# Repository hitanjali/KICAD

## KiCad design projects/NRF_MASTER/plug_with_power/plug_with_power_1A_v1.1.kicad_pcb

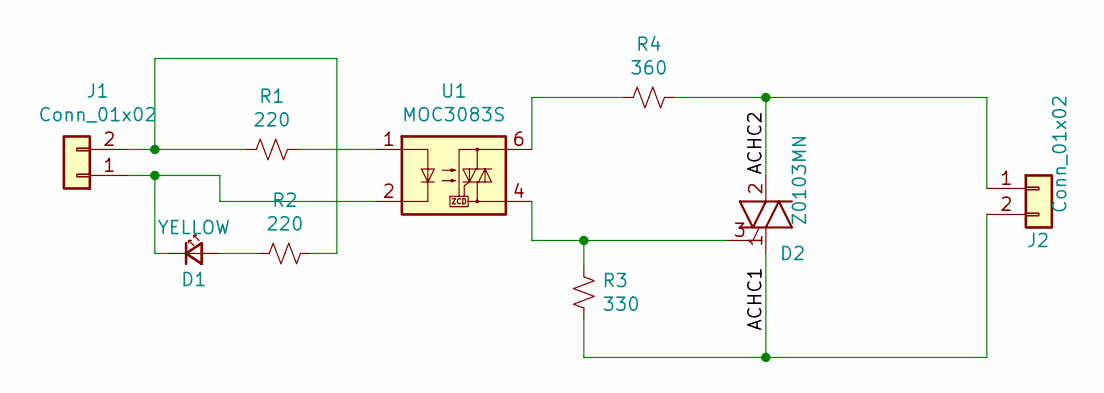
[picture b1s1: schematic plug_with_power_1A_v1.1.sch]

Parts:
D1: YELLOW; LED_0603_1608Metric
D2: Z0103MN; SOT-223
J1: Conn_01x02; PinHeader_1x02_P2.54mm_Vertical
J2: Conn_01x02; Molex_KK-396_A-41791-0002_1x02_P3.96mm_Vertical
R1, R2: 220; R_0603_1608Metric
R3: 330; R_0603_1608Metric
R4: 360; R_0603_1608Metric
U1: MOC3083S; SMDIP-6_W9.53mm_Clearance8mm

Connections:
/ACHC1: D2.1 (A1), J2.2, R3.1
/ACHC2: D2.2 (A2), D2.4 (A4), J2.1, R4.1
unnamed: D1.1 (K), J1.1, U1.2
unnamed: D1.2 (A), R2.2
unnamed: D2.3 (G), R3.2, U1.4
unnamed: J1.2, R1.2, R2.1
unnamed: R1.1, U1.1
unnamed: R4.2, U1.6

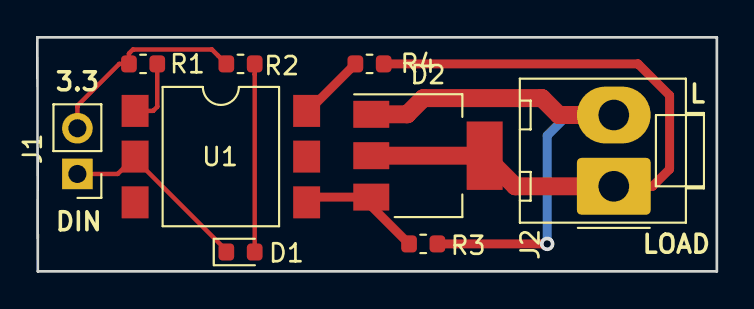
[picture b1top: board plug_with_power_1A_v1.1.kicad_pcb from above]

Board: 2 copper layers, 37.8 x 13.0 mm, 9 parts (0 on the bottom side), 8 nets.

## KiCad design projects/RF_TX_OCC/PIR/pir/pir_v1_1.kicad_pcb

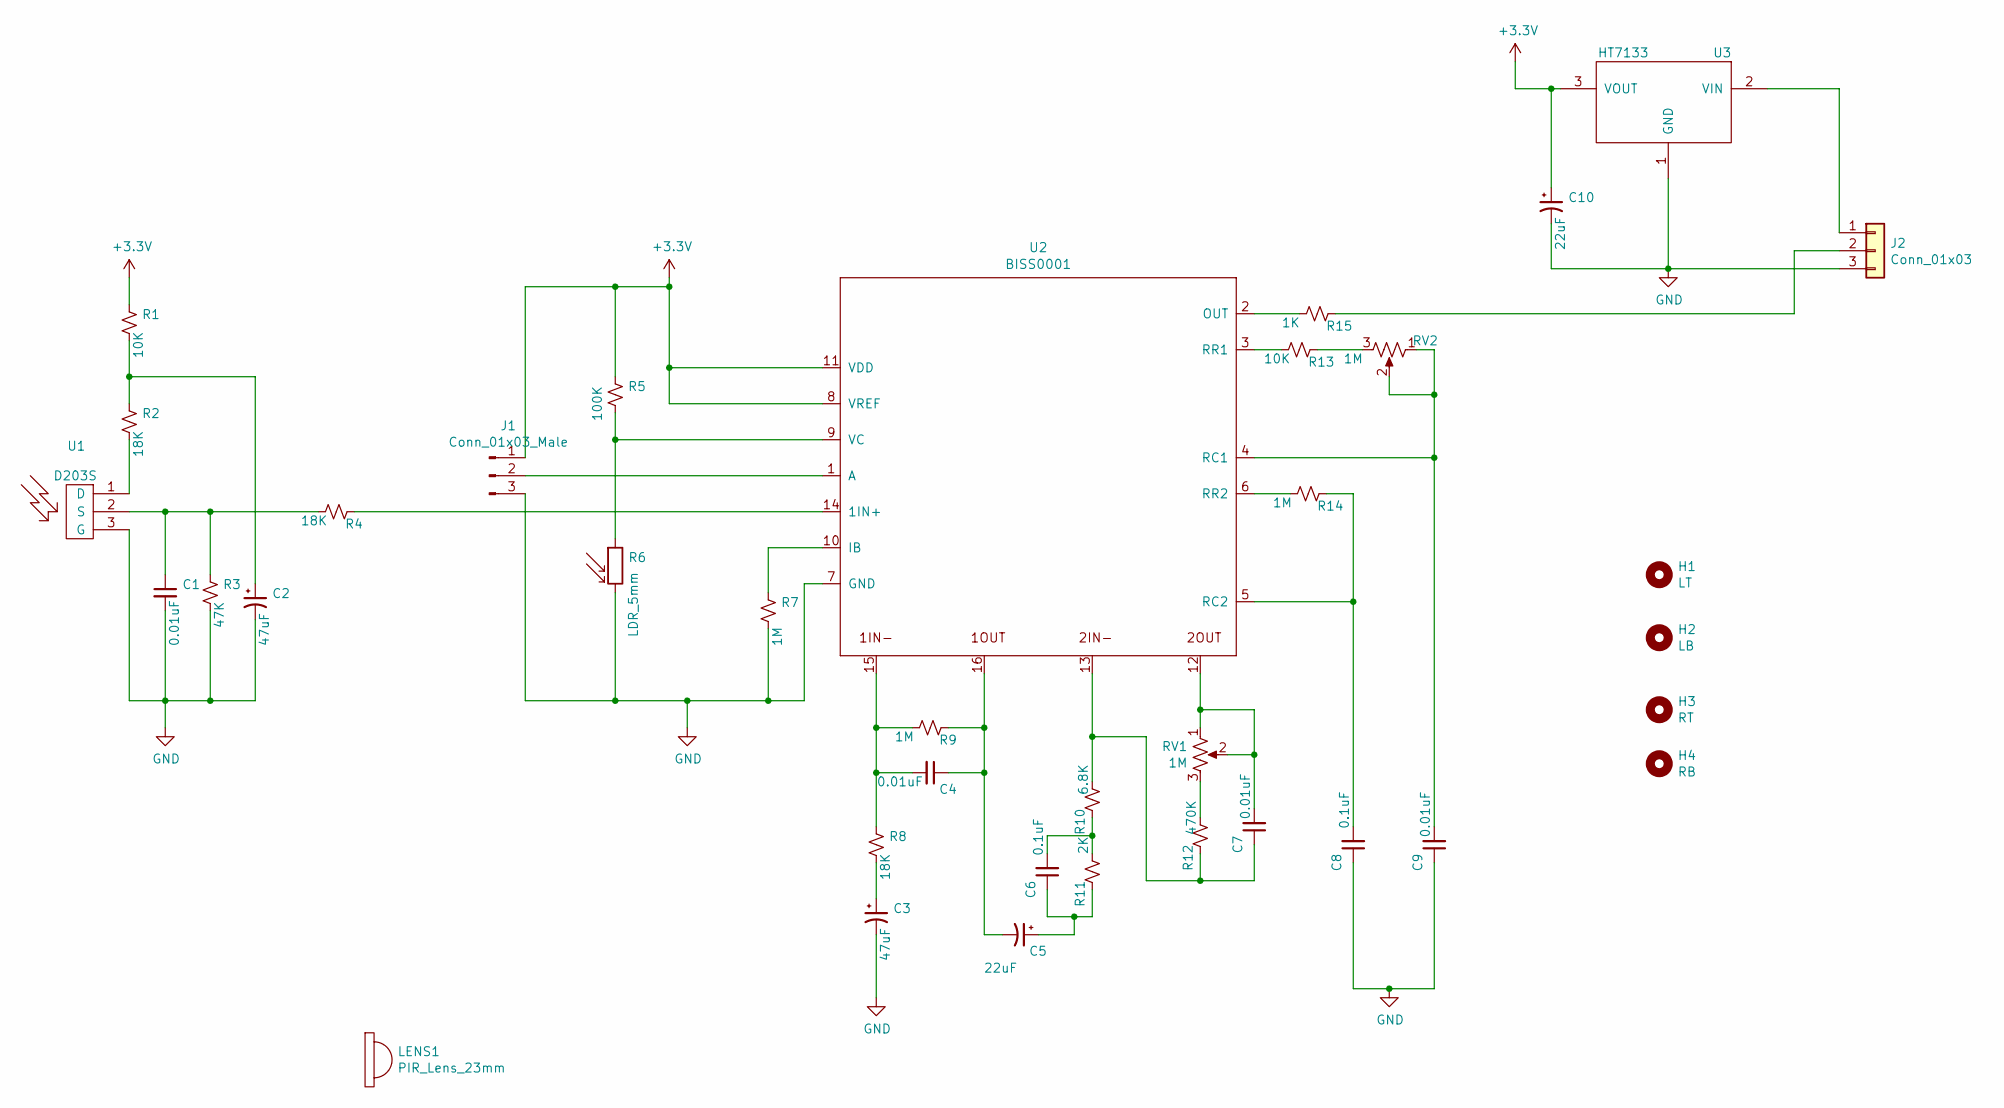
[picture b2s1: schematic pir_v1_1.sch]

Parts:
C1, C4, C7, C9: 0.01uF; C_0402_1005Metric
C2, C3: 47uF; CP_Radial_D5.0mm_P2.50mm
C5, C10: 22uF; CP_Radial_D5.0mm_P2.50mm
C6, C8: 0.1uF; C_0402_1005Metric
H1: LT; MountingHole_2.1mm
H2: LB; MountingHole_2.1mm
H3: RT; MountingHole_2.1mm
H4: RB; MountingHole_2.1mm
J1: Conn_01x03_Male; SolderJumper-3_P1.3mm_Open_RoundedPad1.0x1.5mm
J2: Conn_01x03; PinHeader_1x03_P2.54mm_Vertical
LENS1: PIR_Lens_23mm
R1, R13: 10K; R_0402_1005Metric
R2, R4, R8: 18K; R_0402_1005Metric
R3: 47K; R_0402_1005Metric
R5: 100K; R_0402_1005Metric
R6: LDR_5mm; R_LDR_5.0x4.1mm_P3mm_Vertical
R7, R9, R14: 1M; R_0402_1005Metric
R10: 6.8K; R_0402_1005Metric
R11: 2K; R_0402_1005Metric
R12: 470K; R_0402_1005Metric
R15: 1K; R_0402_1005Metric
RV1, RV2: 1M; Potentiometer_Runtron_RM-063_Horizontal
U1: D203S; TO-5-3_Window
U2: BISS0001; STC_SOP-16_3.9x9.9mm_P1.27mm
U3: HT7133; SOT-89-3

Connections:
+3V3: C10.1, J1.1, R1.1, R5.1, U2.8 (VREF), U2.11 (VDD), U3.3 (VOUT)
GND: C1.2, C2.2, C3.2, C8.1, C9.1, C10.2, J1.3, J2.3, R3.2, R6.2, R7.2, U1.3 (G), U2.7 (GND), U3.1 (GND)
unnamed: C1.1, R3.1, R4.2, U1.2 (S)
unnamed: C2.1, R1.2, R2.1
unnamed: C3.1, R8.2
unnamed: C4.1, C5.2, R9.1, U2.16 (1OUT)
unnamed: C4.2, R8.1, R9.2, U2.15 (1IN-)
unnamed: C5.1, C6.1, R11.1
unnamed: C6.2, R10.1, R11.2
unnamed: C7.1, R10.2, R12.1, U2.13 (2IN-)
unnamed: C7.2, RV1.1, RV1.2, U2.12 (2OUT)
unnamed: C8.2, R14.1, U2.5 (RC2)
unnamed: C9.2, RV2.1, RV2.2, U2.4 (RC1)
unnamed: J1.2, U2.1 (A)
unnamed: J2.1, U3.2 (VIN)
unnamed: J2.2, R15.1
unnamed: R2.2, U1.1 (D)
unnamed: R4.1, U2.14 (1IN+)
unnamed: R5.2, R6.1, U2.9 (VC)
unnamed: R7.1, U2.10 (IB)
unnamed: R12.2, RV1.3
unnamed: R13.1, RV2.3
unnamed: R13.2, U2.3 (RR1)
unnamed: R14.2, U2.6 (RR2)
unnamed: R15.2, U2.2 (OUT)

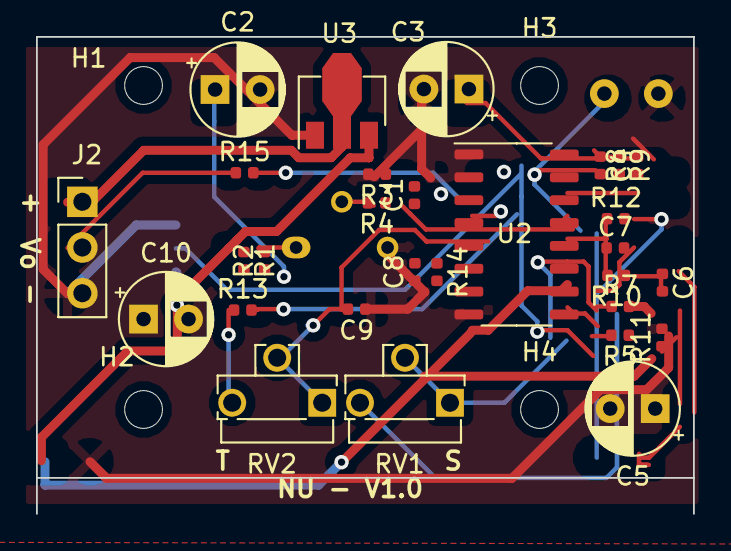
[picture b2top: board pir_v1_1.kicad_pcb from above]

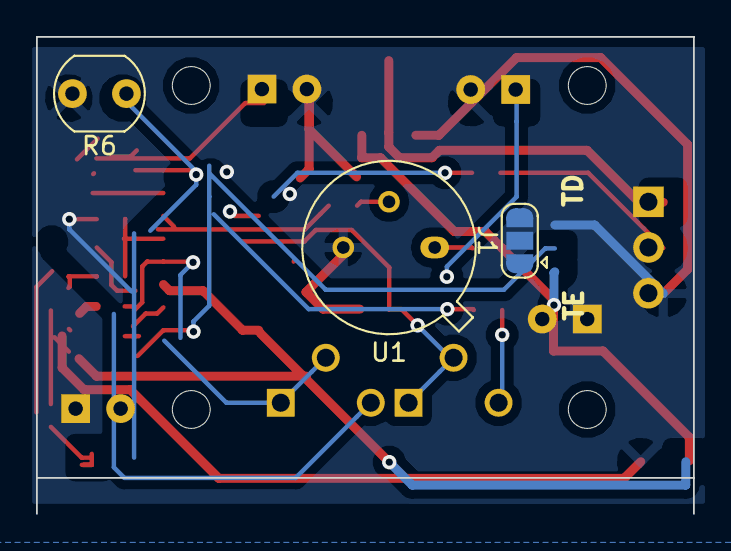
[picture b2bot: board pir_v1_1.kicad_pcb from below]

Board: 2 copper layers, 36.5 x 26.5 mm, 36 parts (3 on the bottom side), 25 nets.

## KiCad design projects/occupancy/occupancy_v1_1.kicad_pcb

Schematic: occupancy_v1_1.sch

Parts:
C1: 470uF16V-8X12; CP_Radial_D8.0mm_P3.50mm
C2: 103-50V; C_Disc_D3.0mm_W1.6mm_P2.50mm
C3: 10UF16V-5X11; CP_Radial_D4.0mm_P1.50mm
D1: 1N4001; D_DO-41_SOD81_P10.16mm_Horizontal
J1, J3, J4, J5: Conn_01x01; SolderWirePad_1x01_Drill1.5mm
J2: CONN0103; PinHeader_1x03_P2.54mm_Vertical
K1: SRD-05VDC-SL-C; Relay_SPDT_SANYOU_SRD_Series_Form_C
PCB1: HC-SR501
Q1: BC547; TO-92_Wide
R1: LDR5528; R_Axial_DIN0204_L3.6mm_D1.6mm_P5.08mm_Horizontal
R2: 10K0.25W; R_Axial_DIN0207_L6.3mm_D2.5mm_P10.16mm_Horizontal
RV1: 3296W-203; Potentiometer_Bourns_3296W_Vertical
U1: Easy-Power; EASY-POWER
U2: NE555P; DIP-8_W7.62mm_LongPads

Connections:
GNDREF: C1.2, C2.2, C3.2, J2.1, Q1.3 (E), RV1.3, U1.3 (Vo-), U2.1 (GND), U2.6 (THR)
unnamed: C2.1, U2.5 (CV)
unnamed: C3.1, Q1.2 (B), R2.1
unnamed: D1.2 (A), K1.2, Q1.1 (C)
unnamed: J1.1, K1.1, U1.1 (AC)
unnamed: J2.2, U2.4 (R)
unnamed: J3.1, K1.3
unnamed: J4.1, K1.4
unnamed: J5.1, U1.2 (AC)
unnamed: R1.2, RV1.2, U2.2 (TR)
unnamed: R2.2, U2.3 (Q)
VCC: C1.1, D1.1 (K), J2.3, K1.5, R1.1, U1.4 (Vo+), U2.8 (VCC)

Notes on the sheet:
As per the GP Box

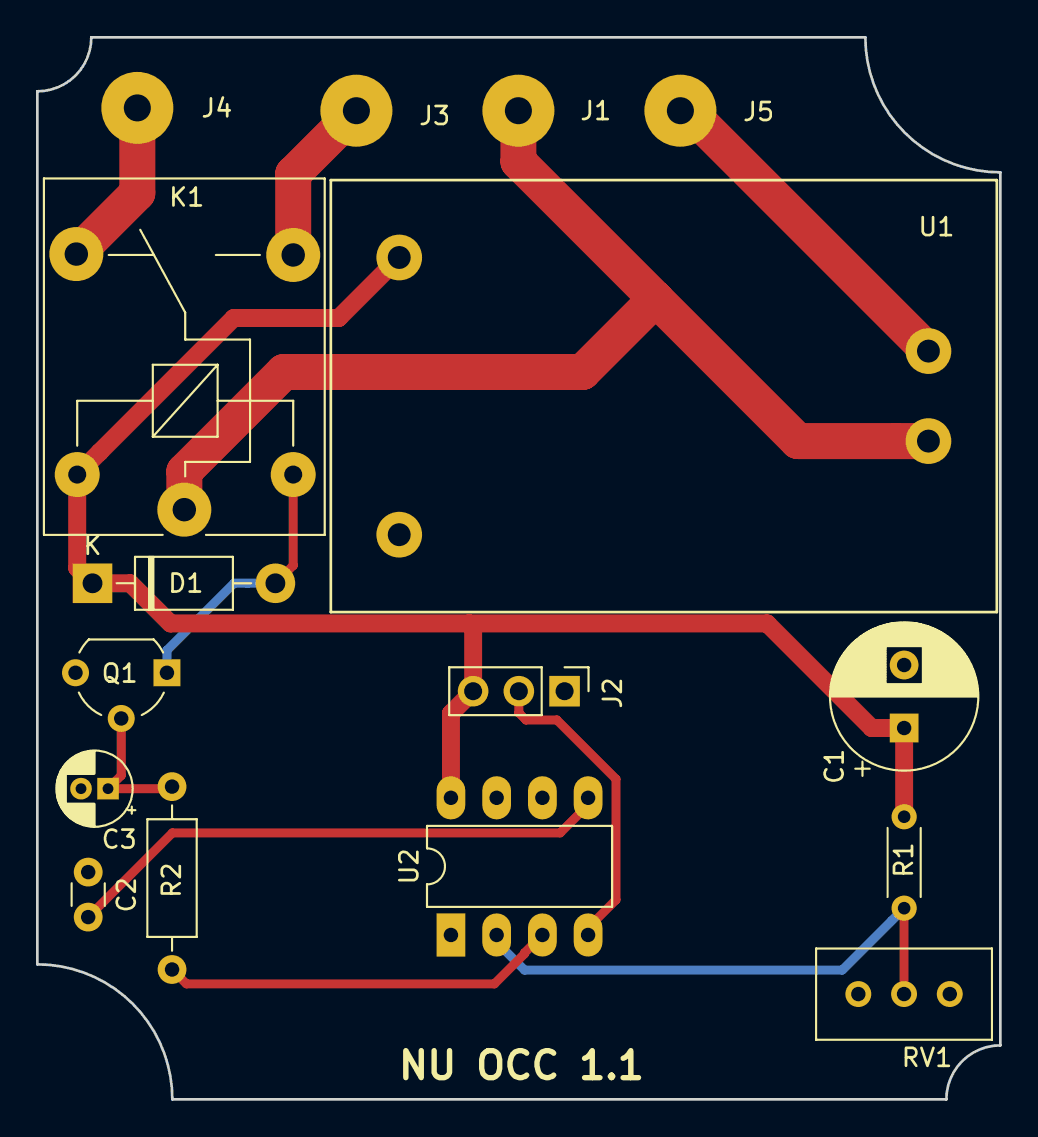
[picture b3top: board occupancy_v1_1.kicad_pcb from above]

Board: 2 copper layers, 53.5 x 59.0 mm, 16 parts (0 on the bottom side), 12 nets.

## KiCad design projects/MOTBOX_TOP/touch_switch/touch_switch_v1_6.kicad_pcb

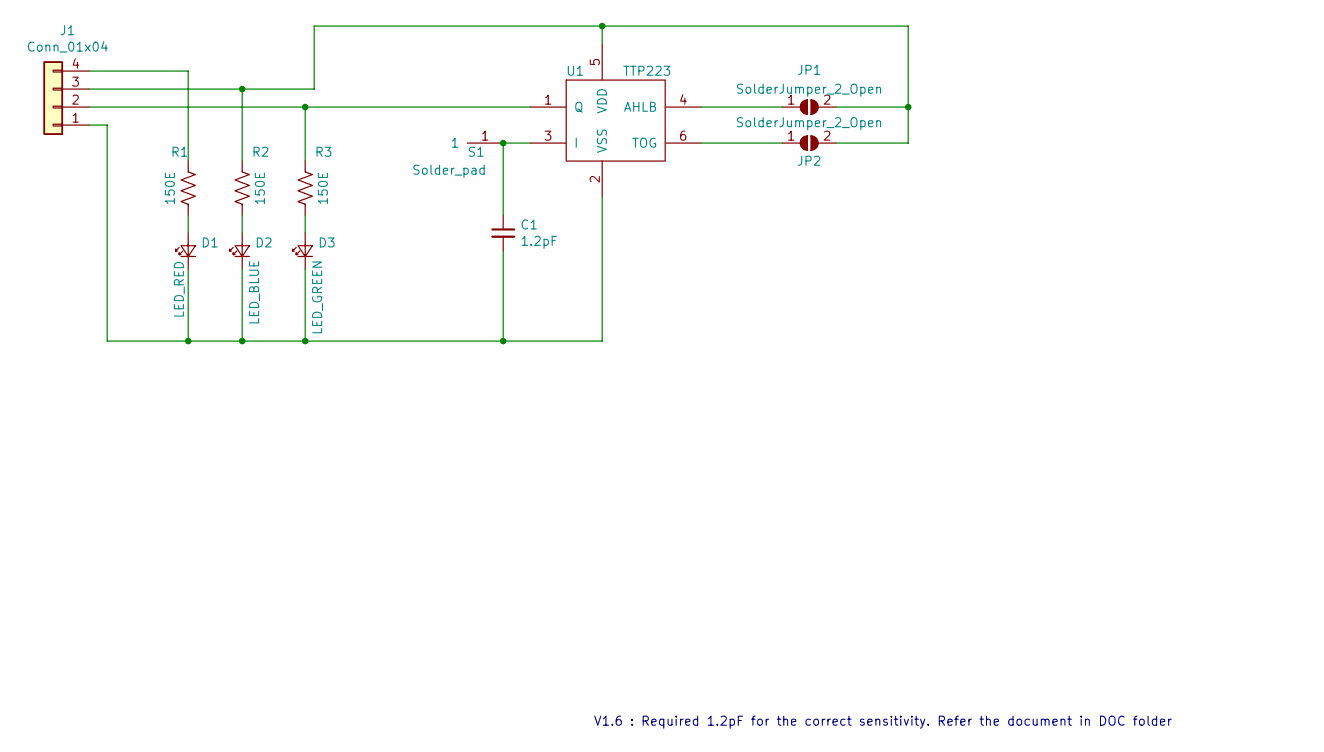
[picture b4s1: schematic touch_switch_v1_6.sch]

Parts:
C1: 1.2pF; C_0603_1608Metric
D1: LED_RED; LED_0603_1608Metric
D2: LED_BLUE; LED_0603_1608Metric
D3: LED_GREEN; LED_0603_1608Metric
J1: Conn_01x04; SolderWirePad_1x04_P3.175mm_Drill0.8mm
JP1, JP2: SolderJumper_2_Open; SolderJumper-2_P1.3mm_Open_RoundedPad1.0x1.5mm
R1, R2, R3: 150E; R_0603_1608Metric
S1: Solder_pad; Touch_pad_with_backlight
U1: TTP223; SOT-23-6

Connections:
unnamed: C1.1, S1.1, U1.3 (I)
unnamed: C1.2, D1.1 (K), D2.1 (K), D3.1 (K), J1.1, U1.2 (VSS)
unnamed: D1.2 (A), R1.2
unnamed: D2.2 (A), R2.2
unnamed: D3.2 (A), R3.2
unnamed: J1.2, R3.1, U1.1 (Q)
unnamed: J1.3, JP1.2 (B), JP2.2 (B), R2.1, U1.5 (VDD)
unnamed: J1.4, R1.1
unnamed: JP1.1 (A), U1.4 (AHLB)
unnamed: JP2.1 (A), U1.6 (TOG)

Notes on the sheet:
V1.6 : Required 1.2pF for the correct sensitivity. Refer the document in DOC folder

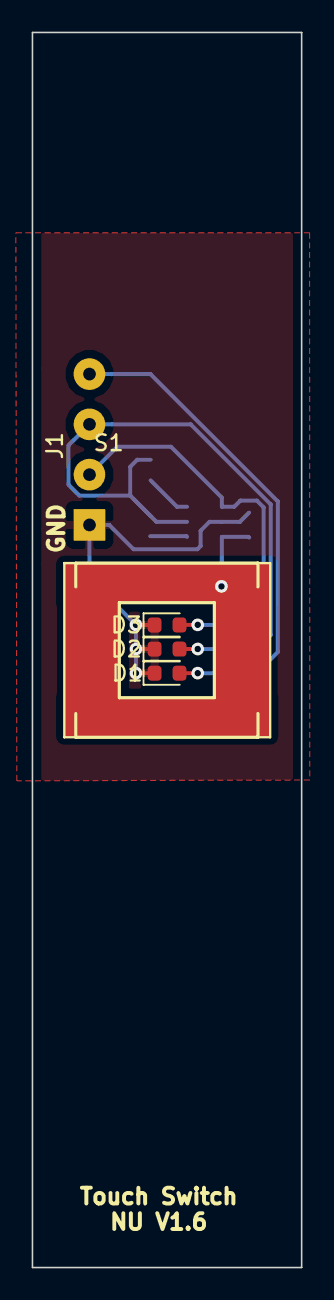
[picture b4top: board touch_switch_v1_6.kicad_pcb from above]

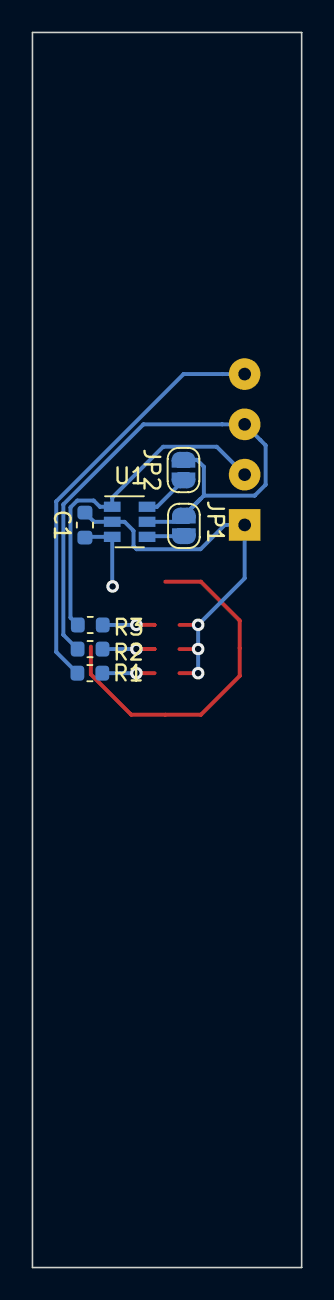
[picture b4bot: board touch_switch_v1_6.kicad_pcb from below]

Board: 2 copper layers, 17.0 x 78.0 mm, 12 parts (7 on the bottom side), 10 nets.

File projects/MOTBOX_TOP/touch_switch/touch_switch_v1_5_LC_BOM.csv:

S.No,Manufacturing Part No,Designator,Quantity,Description(VALUE),Package(CASE),Top/Bottom,Points (No. of Pins),Comments,,
1,  , "C1, " , "1" , "30pF" , "Capacitor_SMD:C_0603_1608Metric" , TOP , 2, "Unpolarized capacitor, small symbol", , 
2,  , "D1, " , "1" , "LED_RED" , "LED_SMD:LED_0603_1608Metric" , TOP , 2, "Light emitting diode, small symbol", , 
3,  , "D2, " , "1" , "LED_GREEN" , "LED_SMD:LED_0603_1608Metric" , TOP , 2, "Light emitting diode, small symbol", , 
4,  , "D3, " , "1" , "LED_BLUE" , "LED_SMD:LED_0603_1608Metric" , TOP , 2, "Light emitting diode, small symbol", , 
5,  , "J1, " , "1" , "Conn_01x04" , "Connector_Wire:SolderWirePad_1x04_P3.175mm_Drill0.8mm" , TOP , 4, "Generic connector, single row, 01x04, script generated (kicad-library-utils/schlib/autogen/connector/)", , 
6,  , "JP1, JP2, " , "2" , "SolderJumper_2_Open" , "Jumper:SolderJumper-2_P1.3mm_Open_RoundedPad1.0x1.5mm" , TOP , 2, "Solder Jumper, 2-pole, open", , 
7,  , "R1, R2, R3, " , "3" , "150E" , "Resistor_SMD:R_0603_1608Metric" , TOP , 2, "Resistor, US symbol", , 
8,  , "S1, " , "1" , "Solder_pad" , "mylib:Touch_pad_10x10mm" , TOP , 1, "", , 
9,  , "U1, " , "1" , "TTP223" , "Package_TO_SOT_SMD:SOT-23-6" , TOP , 6, "", ,

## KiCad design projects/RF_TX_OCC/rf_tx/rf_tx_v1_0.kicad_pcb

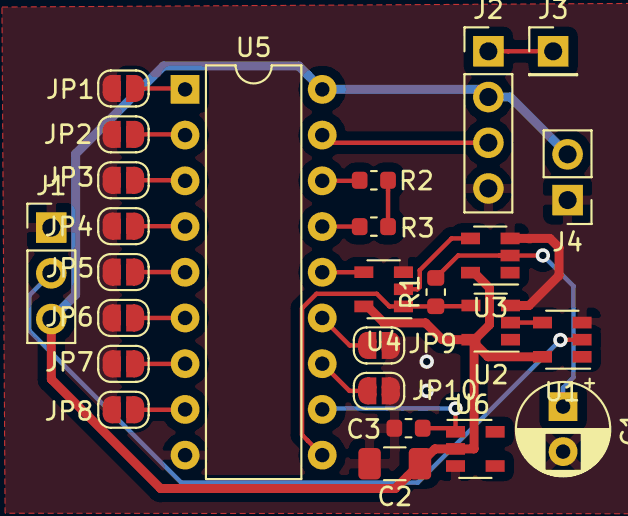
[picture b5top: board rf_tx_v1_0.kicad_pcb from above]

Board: 2 copper layers, 26 parts (0 on the bottom side), 24 nets.

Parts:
C1: 330uF; CP_Radial_D5.0mm_P2.50mm
C2: 1uF; C_1206_3216Metric
C3: 100pF; C_0603_1608Metric
J1: Conn_01x03; PinHeader_1x03_P2.54mm_Vertical
J2: Conn_01x04; PinHeader_1x04_P2.54mm_Vertical
J3: Conn_01x01_Female; PinHeader_1x01_P2.54mm_Vertical
J4: Conn_01x02; PinHeader_1x02_P2.54mm_Vertical
JP1, JP2, JP3, JP4, JP5, JP6, JP7, JP8, JP9, JP10: Jumper_NO_Small; SolderJumper-2_P1.3mm_Open_RoundedPad1.0x1.5mm
R1: 1K; R_0603_1608Metric
R2: 100K; R_0603_1608Metric
R3: 1M; R_0603_1608Metric
U1, U2: 74LVC1G04; SOT-23-5
U3: 74LVC1G14; SOT-23-5
U4: 74LVC1G86; SOT-23-5
U5: HT12E; DIP-18_W7.62mm
U6: BD49ExxG; SOT-23-5

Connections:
/ANT: J2.1, J3.1
/BAT_LOW_N: C3.1, U5.11, U6.1
/DATA: J2.3, U5.17
/SENSOR: J1.2, U1.2
/SENSOR_LS: R1.1, U2.4, U4.1, U5.10
GND: C1.2, C2.2, C3.2, J1.1, J2.4, J4.1, JP1.1, JP2.1, JP3.1, JP4.1, JP5.1, JP6.1, JP7.1, JP8.1, JP9.2, JP10.2, U1.3, U2.3, U3.3, U4.3, U5.9, U6.3
unnamed: C1.1, R1.2, U3.2
unnamed: JP1.2, U5.1
unnamed: JP2.2, U5.2
unnamed: JP3.2, U5.3
unnamed: JP4.2, U5.4
unnamed: JP5.2, U5.5
unnamed: JP6.2, U5.6
unnamed: JP7.2, U5.7
unnamed: JP8.2, U5.8
unnamed: JP9.1, U5.13
unnamed: JP10.1, U5.12
unnamed: R2.1, R3.1
unnamed: R2.2, U5.16
unnamed: R3.2, U5.15
unnamed: U1.4, U2.2
unnamed: U3.4, U4.2
unnamed: U4.4, U5.14
VCC: C2.1, J1.3, J2.2, J4.2, U1.5, U2.5, U3.5, U4.5, U5.18, U6.2

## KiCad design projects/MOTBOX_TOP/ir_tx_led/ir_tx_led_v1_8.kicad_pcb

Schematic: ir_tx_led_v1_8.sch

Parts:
D1, D2, D3: IR333-A; LED_D5.0mm_Horizontal_O6.35mm_Z9.0mm
H1, H2, H3, H4: MountingHole; MountingHole_3.2mm_M3_DIN965
H5, H6, H7: MountingHole; MountingHole_2.2mm_M2_DIN965
J1: Conn_01x04; PinHeader_1x04_P2.54mm_Vertical

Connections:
unnamed: D1.1 (K), D2.1 (K), D3.1 (K), J1.1
unnamed: D1.2 (A), J1.4
unnamed: D2.2 (A), J1.3
unnamed: D3.2 (A), J1.2

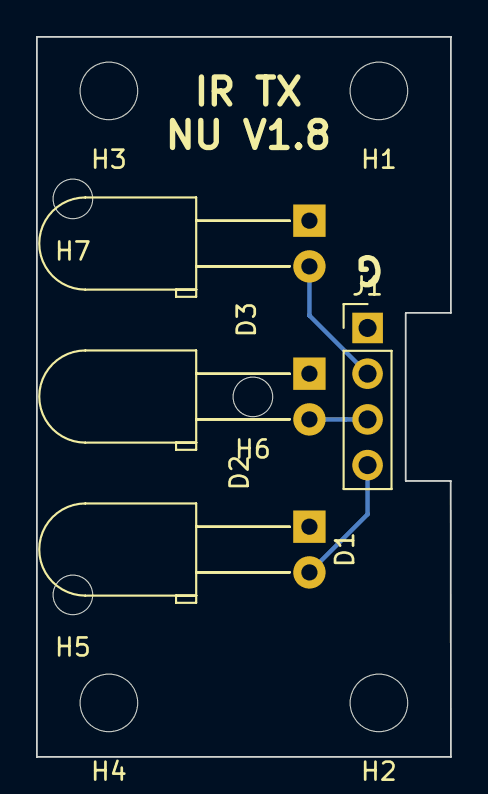
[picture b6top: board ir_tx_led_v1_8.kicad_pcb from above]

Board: 2 copper layers, 23.0 x 40.0 mm, 11 parts (0 on the bottom side), 4 nets.

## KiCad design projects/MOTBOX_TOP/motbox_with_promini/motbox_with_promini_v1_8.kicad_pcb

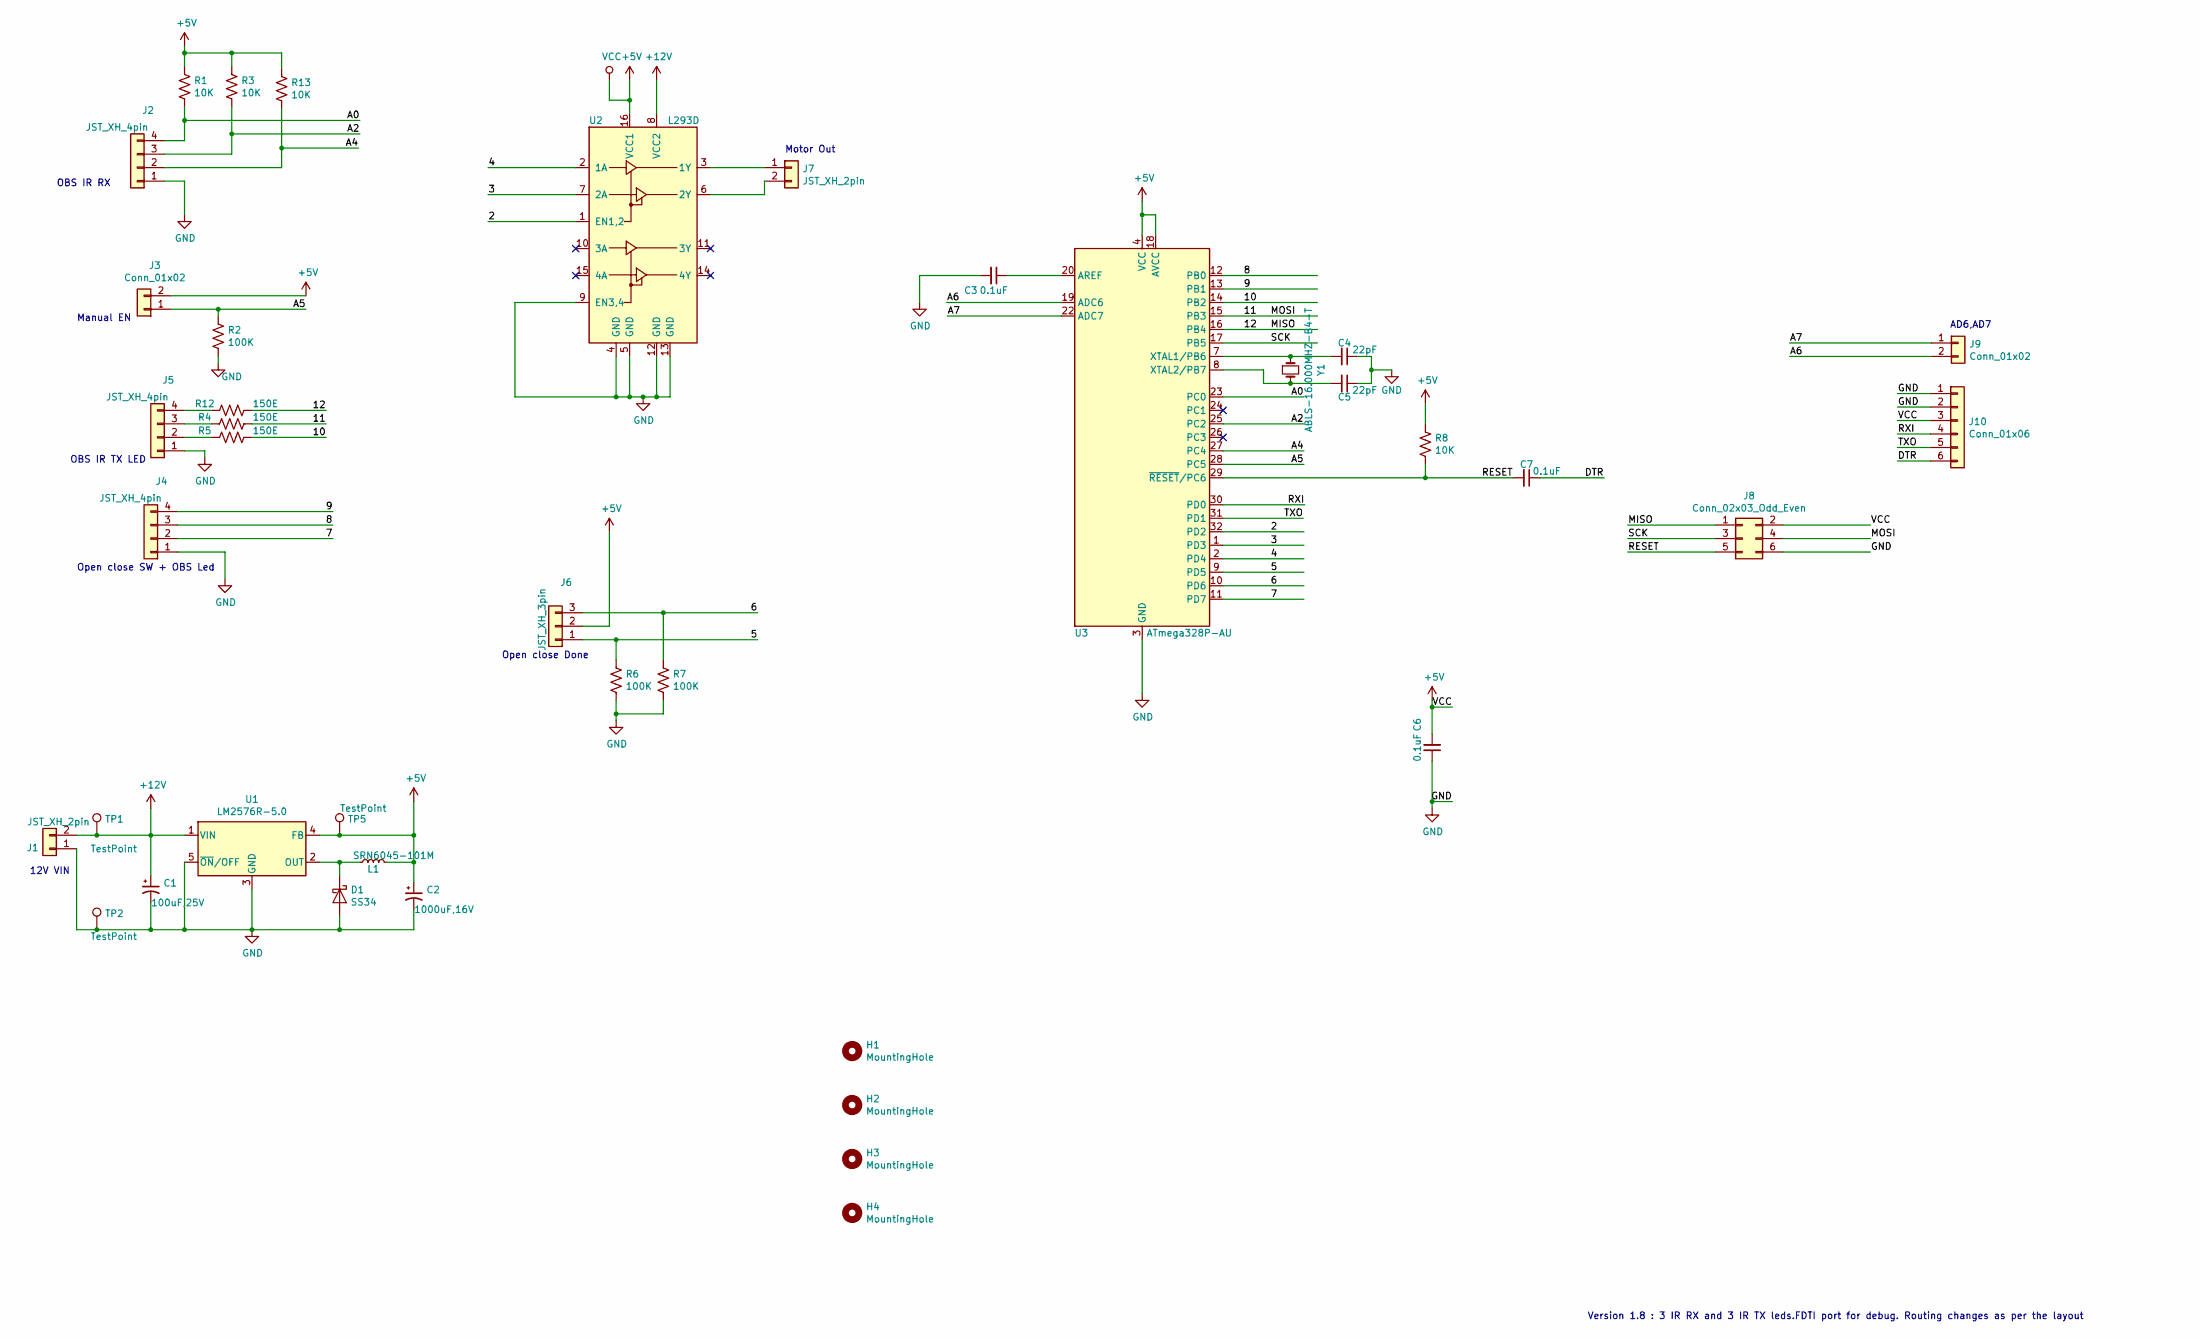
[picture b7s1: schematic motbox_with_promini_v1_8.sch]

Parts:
C1: 100uF,25V; CP_Radial_D6.3mm_P2.50mm
C2: 1000uF,16V; CP_Radial_D10.0mm_P5.00mm
C3, C6, C7: 0.1uF; C_0603_1608Metric
C4, C5: 22pF; C_0603_1608Metric
D1: SS34; D_SMC
H1, H2, H3, H4: MountingHole; MountingHole_2.2mm_M2_ISO7380
J1, J7: JST_XH_2pin; JST_XH_B2B-XH-A_1x02_P2.50mm_Vertical
J2, J4, J5: JST_XH_4pin; JST_XH_B4B-XH-A_1x04_P2.50mm_Vertical
J3, J9: Conn_01x02; PinHeader_1x02_P2.54mm_Vertical
J6: JST_XH_3pin; JST_XH_B3B-XH-A_1x03_P2.50mm_Vertical
J8: Conn_02x03_Odd_Even; PinHeader_2x03_P2.54mm_Vertical
J10: Conn_01x06; PinHeader_1x06_P2.54mm_Vertical
L1: SRN6045-101M; L_Bourns_SRN6045TA
R1, R3, R8, R13: 10K; R_0603_1608Metric
R2, R6, R7: 100K; R_0603_1608Metric
R4, R5, R12: 150E; R_0603_1608Metric
TP1, TP2, TP5: TestPoint; TestPoint_Pad_1.0x1.0mm
U1: LM2576R-5.0; TO-263-5_TabPin3
U2: L293D; DIP-16_W7.62mm
U3: ATmega328P-AU; TQFP-32_7x7mm_P0.8mm
Y1: ABLS-16.000MHZ-B4-T; Crystal_SMD_HC49-SD

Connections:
+5V: C2.1, C6.2, J3.2, J6.2, J8.2, J10.3, L1.2, R1.1, R3.1, R8.1, R13.1, TP5.1, U1.4 (FB), U2.16 (VCC1), U3.4 (VCC), U3.6 (VCC), U3.18 (AVCC)
+12V: C1.1, J1.2, TP1.1, U1.1 (VIN), U2.8 (VCC2)
/2: U2.1 (EN1,2), U3.32 (PD2)
/3: U2.7 (2A), U3.1 (PD3)
/4: U2.2 (1A), U3.2 (PD4)
/5: J6.1, R6.1, U3.9 (PD5)
/6: J6.3, R7.1, U3.10 (PD6)
/7: J4.2, U3.11 (PD7)
/8: J4.3, U3.12 (PB0)
/9: J4.4, U3.13 (PB1)
/10: R5.1, U3.14 (PB2)
/11: J8.4, R4.1, U3.15 (PB3)
/12: J8.1, R12.1, U3.16 (PB4)
/A0: J2.4, R1.2, U3.23 (PC0)
/A2: J2.3, R3.2, U3.25 (PC2)
/A4: J2.2, R13.2, U3.27 (PC4)
/A5: J3.1, R2.1, U3.28 (PC5)
/A6: J9.2, U3.19 (ADC6)
/A7: J9.1, U3.22 (ADC7)
/DTR: C7.1, J10.6
/RESET: C7.2, J8.5, R8.2, U3.29 (~RESET~/PC6)
/RXI: J10.4, U3.30 (PD0)
/SCK: J8.3, U3.17 (PB5)
/TXO: J10.5, U3.31 (PD1)
GND: C1.2, C2.2, C3.2, C4.1, C5.1, C6.1, D1.2 (A), J1.1, J2.1, J4.1, J5.1, J8.6, J10.1, J10.2, R2.2, R6.2, R7.2, TP2.1, U1.3 (GND), U1.5 (~ON~/OFF), U2.4 (GND), U2.5 (GND), U2.9 (EN3,4), U2.12 (GND), U2.13 (GND), U3.3 (GND), U3.5 (GND), U3.21 (GND)
unnamed: C3.1, U3.20 (AREF)
unnamed: C4.2, U3.7 (XTAL1/PB6), Y1.1
unnamed: C5.2, U3.8 (XTAL2/PB7), Y1.2
unnamed: D1.1 (K), L1.1, U1.2 (OUT)
unnamed: J5.2, R5.2
unnamed: J5.3, R4.2
unnamed: J5.4, R12.2
unnamed: J7.1, U2.3 (1Y)
unnamed: J7.2, U2.6 (2Y)

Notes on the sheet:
Version 1.8 : 3 IR RX and 3 IR TX leds.FDTI port for debug. Routing changes as per the layout
OBS IR RX
OBS IR TX LED
Manual EN
Open close SW + OBS Led
12V VIN
Open close Done
Motor Out
AD6,AD7

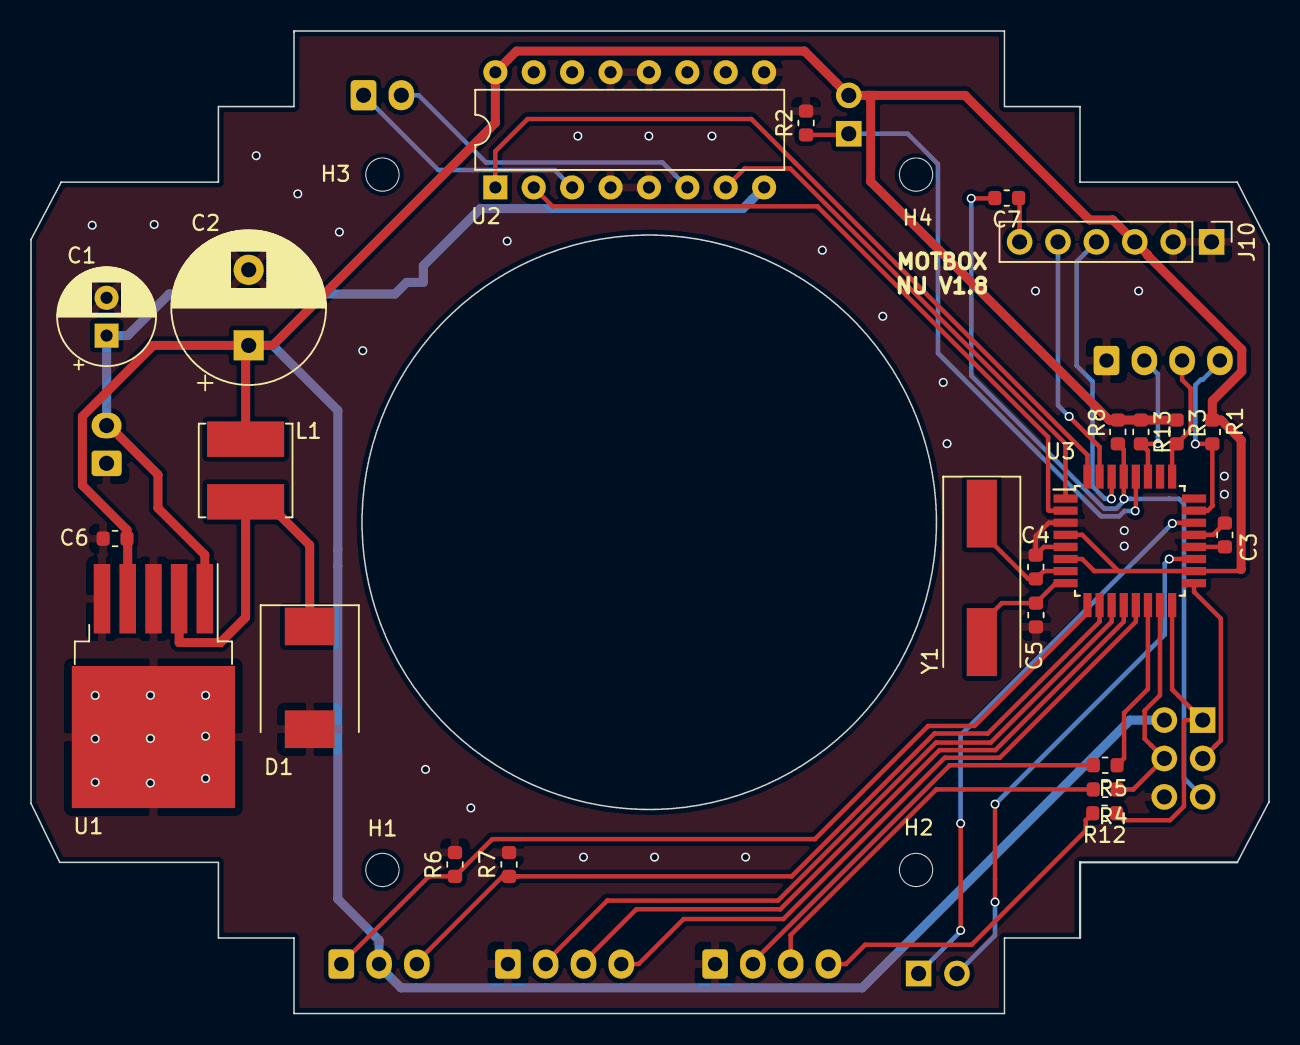
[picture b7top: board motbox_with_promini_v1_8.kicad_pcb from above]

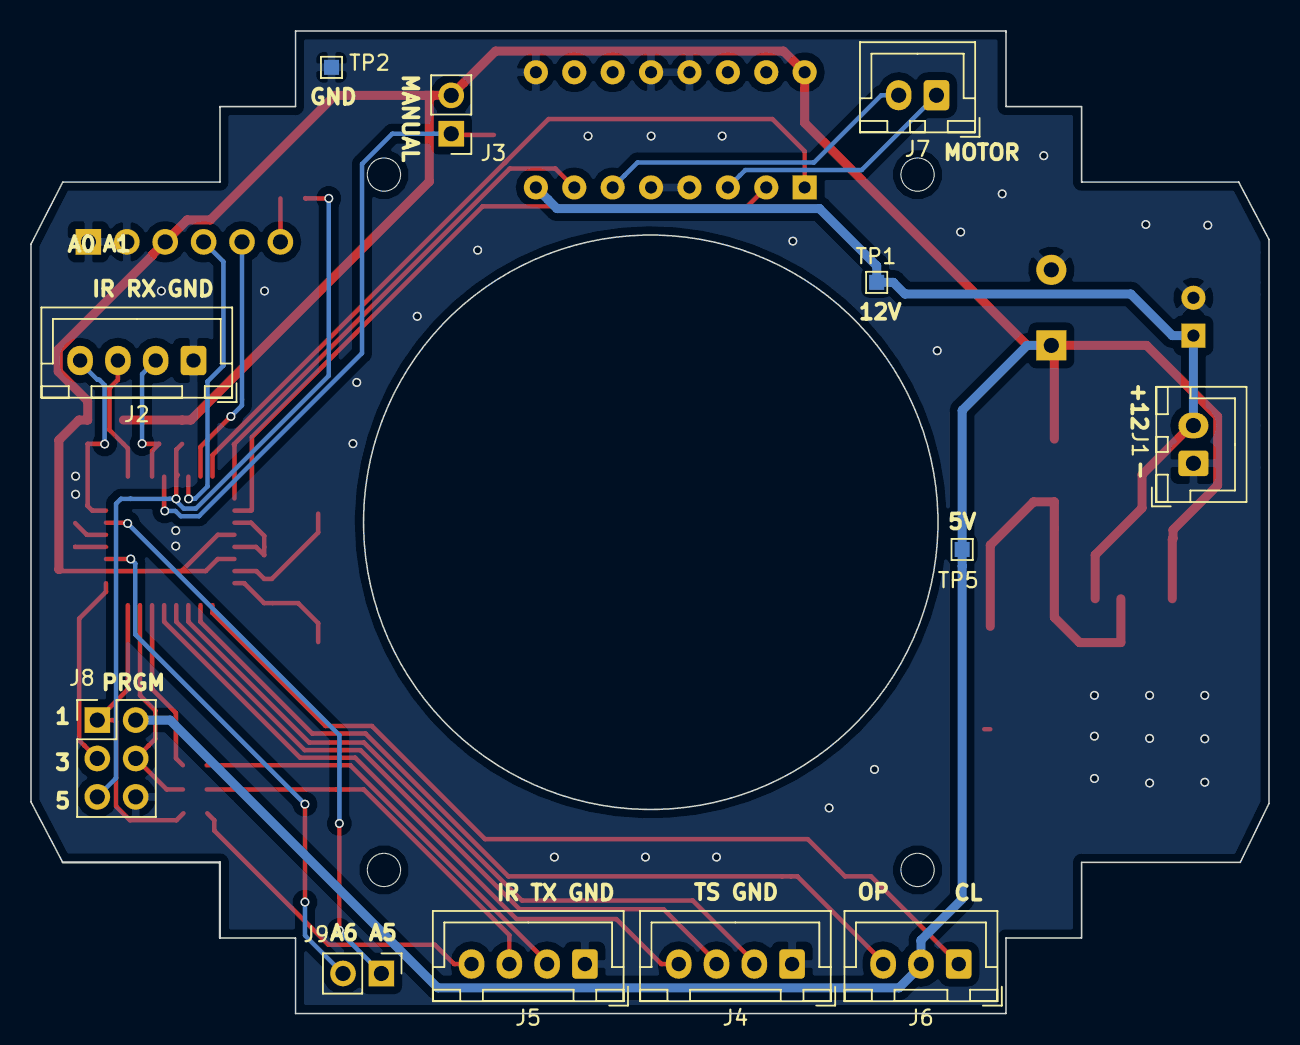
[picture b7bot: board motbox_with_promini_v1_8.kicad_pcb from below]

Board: 2 copper layers, 81.9 x 65.0 mm, 40 parts (12 on the bottom side), 34 nets.

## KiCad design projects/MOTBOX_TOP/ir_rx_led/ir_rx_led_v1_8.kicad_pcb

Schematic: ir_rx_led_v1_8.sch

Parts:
D1, D2, D3: PD333-3B/H0/L2; LED_D5.0mm_Horizontal_O6.35mm_Z9.0mm
H1, H2, H3, H4: MountingHole; MountingHole_3.2mm_M3_DIN965
H5, H6, H7: MountingHole; MountingHole_2.2mm_M2_DIN965
J1: Conn_01x04; PinHeader_1x04_P2.54mm_Vertical

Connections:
unnamed: D1.1 (K), J1.2
unnamed: D1.2 (A), D2.2 (A), D3.2 (A), J1.1
unnamed: D2.1 (K), J1.3
unnamed: D3.1 (K), J1.4

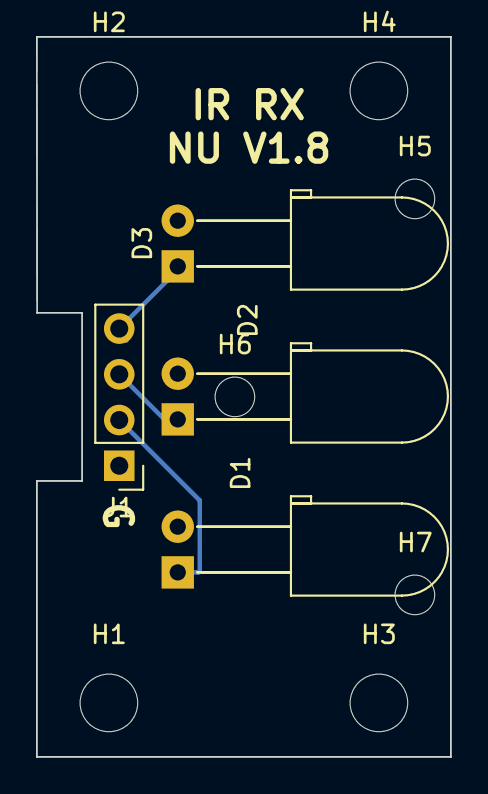
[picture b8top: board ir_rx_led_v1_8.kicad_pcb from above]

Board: 2 copper layers, 23.0 x 40.0 mm, 11 parts (0 on the bottom side), 4 nets.

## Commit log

2019-03-29 Added all the kicad files for the first time
2019-04-15 Changed mode to all 777
2019-04-30 added new custom symbols and non pcb objects
2019-04-30 Many new files and motbox related changes mostly
2019-05-03 Changes for the motbox with promini instead of nano
2019-05-03 Changes in motbox with the promini instead of nano
2019-05-07 Seems to be final version with promini
2019-05-10 Script to generate the LC BOM file for PCB
2019-05-10 Gerber files added
2019-06-05 New library files and schematics with ESE31 and DT045 switches
2019-06-05 ESE31 and DT045 related schematic changes
2019-06-10 Libparts with no pins like mounting hole changes
2019-06-10 Connector on back and mounting holes added
2019-06-10 Touch switch with feedback light changes
2019-06-10 removing gerber files from repo not needed
2019-07-02 Version 1.4 for layout changes related to 12V gnd
2019-07-02 Top schematics
2019-07-02 Touch switch changes for dual color led
2019-07-29 Version 1.5 schematic and related files
2019-07-29 Version 1.5 related changes
2019-07-29 Arduino on the PCV and A0 A1 related changes
2019-07-29 Version 1.4
2019-08-08 Added current budget and NOT gate delay exp result
2019-08-16 Single gate adaptor files added
2019-08-16 Added 16 pin DIP GP module files
2019-09-03 Version 1.6 and Version 1.7 added, version notes on the sch page
2019-09-03 tmega board renamed
2019-09-03 Modified the version 1.5 schematic
2019-09-03 Modified v1_5
2019-09-03 Switch PCB is now of 80mm
2019-09-03 New project created for RF transmitter
2019-09-03 added the GP boards
2019-09-04 new symbols added
2019-10-25 For transparent cable detection
2019-10-25 Changes misc
2019-11-05 Changes for improvments
2019-11-05 RF TX for the PIR sensor
2019-11-07 Touch sensitivity experiment observation
2019-11-07 layout wIth the GP box dimensions
2019-12-09 New files modified files etc
2019-12-09 my lib changes
2020-02-03 Cost XLS and v1.1 and changes
2020-09-02 Added MDXS footprint
2020-10-07 Our home made PIR that did not work
2020-10-07 NRF main controller board and sub boards
2020-10-07 Added ZCD
2020-10-12 CBTMN11 and BE33 modules added
2020-10-14 Changes in the module and foot prints
2021-01-22 Switch board changes
2021-02-03 New custom parts
2021-06-03 New footprints for antenna Triac etc
2021-06-03 More symbols in hitesh_custom
2021-09-27 New symbols
2021-10-20 Small FP tactile switch added
    FP added : RKB2JM250MTR_LFS
2021-11-29 New symbols , 3D models and DYULABS logo
